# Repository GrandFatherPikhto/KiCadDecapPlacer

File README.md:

# KiCadSpoke v1.20.0

**KiCadSpoke** is a command-line layout automation and PCB cloning tool for automated placement in **KiCad**, block replication, and routing of components and vias in KiCad based on **templates** and **roles**:

- Moving components (capacitors, resistors, ferrites, crystals, etc.) to specified positions.
- Creating vias attached to the spoke as a whole or to individual components.
- **Cloning** repetitive functional blocks (PI-filters, DAC channels) at different locations on the board.
- Automatic component selection by **roles** and **nets** without specifying explicit refdes.
- Idempotency: repeated runs do not duplicate already correctly placed items.
- Undo of the last operation.
- Extracting templates from the current selection on the board with net parametrisation and custom origin selection.
- Snapshotting channels (for hierarchical projects) via a file‑based cloner (`clone-extract`).
- **Template transformation** (rotation, mirroring, origin shift) using the separate script `transform_template.py`.

---

## Key Features

An advanced script-based alternative to the traditional KiCad Replicate Layout plugin, designed for complex multi-channel projects and automated design reuse via IPC API.

- **Template-based approach** – geometry is described once in local coordinates and can be rotated/translated for each application.
- **Automatic component selection** – instead of refdes, roles are used (`LIGHT`, `HEAVY`, `PI_FILTER_C1`, etc.). Specific instances are taken from a pool by net and the `Role` field in the schematic.
- **Section cloning** (`ClonePlacement`) – supports two modes:
  - **by selection** – for one‑off instances (e.g., a single MCU);
  - **by nets** – for repeatedly repeated blocks (with net name parametrisation via placeholders and `params`). In this mode, ambiguity is resolved by physical proximity to the anchor (if components are electrically indistinguishable but located close to different anchors).
- **Generalised vias** – vias can be at the spoke level and at the component level; all coordinates are relative to the spoke origin, making them independent of actual pad positions.
- **Placement registry** – stores UUIDs of created vias, ensuring idempotency and automatic cleanup of obsolete entries. Now reconciliation is performed against real vias on the board, not only the JSON record, to avoid desynchronisation.
- **Pre‑validation** – config checks before any board modifications (template/pad existence, component pool sufficiency, clone correctness, and resolved via nets existence on the board).
- **Diagnostics** – a set of scripts for debugging IPC, geometry, and field reading.
- **File‑based cloner** (`clone-extract`) – parses `.net` and `.kicad_pcb` without IPC, builds a twin map of channels for hierarchical projects.
- **Template transformation** – the script `utils/transform_template.py` allows rotating, mirroring, and shifting the origin of existing templates without re‑extracting from the board.
- **Enhanced `extract`** – when extracting a template, you can set the origin to a specific via or component (instead of the bbox) and parameterise nets (replace literals with patterns containing placeholders).

---

## Installation and Dependencies

### Requirements
- Python 3.8 or later.
- KiCad 8.0 or later (with IPC API enabled).
- The **kipy** library (Python wrapper for KiCad IPC).

### Installation
```bash
pip install kipy pyyaml sexpdata
```
(For diagnostics, `psutil` may be required.)

### Setting up Roles in the Schematic (Eeschema)
Before using the tool, you need to add a custom field `Role` to components that should participate in placement:
1. Open the symbol in Eeschema.
2. Add a field named **Role** with a value matching the role in the template (e.g., `LIGHT`, `HEAVY`).
3. Run **Update PCB from Schematic** to propagate the field to the board.
4. Verify field readability with the diagnostic script:
   ```bash
   python -m kicadspoke.diagnostics.test_custom_field C5 --field Role
   ```

---

## Key Concepts

### Template (SpokeTemplate)
A template describes the **local geometry** of one "spoke" – a set of components and vias relative to a local origin (0,0) in the `along/across` coordinate system. It contains:
- **`vias`** – vias at the spoke level (usually the power net).
- **`components`** – a list of slots, each with a `role`, local coordinates, angle, and a list of vias (usually to GND).

All coordinates are defined **once** at `rotation_deg=0`; when applied, the template is rotated as a whole.

#### Template layer (`layer`)
Each template now has an absolute layer (`F.Cu` or `B.Cu`), which is automatically set during extraction (`extract`). Components lying on a different layer receive an explicit `layer` in their slot.

#### Net parametrisation during extraction
When extracting a template, you can replace literal net names with patterns containing placeholders using the `--net-template` and `--param` options of the `extract` command. This eliminates manual YAML editing.

### Spoke (ManualSpoke)
Attaches a template to a specific IC pin:
- `pad` – pad number of the target component.
- `shift_x_mm`, `shift_y_mm` – flat shift from the pad centre to the template origin.
- `rotation_deg` – rotation of the entire template.

**Important:** In new config versions, each rule (`rules`) must have its own `anchor_ref` (anchor component). The global `target_ref` has been removed.

### Roles and Component Pool
Instead of refdes, **roles** are used in the config. For each net (`rule.net`), a pool of components is built, where each component:
- Has a `Role` field with the required value.
- Has at least one pad connected to that net.

Components are sorted in natural numeric order (`C5` < `C10`) and consumed in the order of spokes.

### Cloning (ClonePlacement)
Allows applying a template at an arbitrary point on the board, without tying to IC pads. Supports:
- **Selection mode** – reads roles from the current selection in the PCB editor.
- **Net mode** – for each role, a net is specified (via `nets` or `net_template` with placeholders resolved by `params` and `net_overrides`). If multiple candidates are electrically indistinguishable, the tool can pick the one closest to the anchor (if the distance margin is sufficient). This is useful for power filters on a common rail.

### Placement Registry (PlacementRegistry)
Stores each via's UUID, position, parameters, and net in a JSON file next to the config. On subsequent runs:
- already correctly placed vias are skipped;
- those that changed position/parameters are deleted and recreated;
- obsolete entries (keys not present in the new plan) are removed (prune).

**Important:** Reconciliation now checks against real vias on the board (`adapter.get_vias()`), not only the JSON record, preventing desynchronisation due to manual deletions or crashes between registry write and board commit.

### Net Resolution (`net_resolution`)
For cloned templates, net names go through a three‑step resolution:
1. **Literal** – if no placeholders.
2. **Placeholder** – substitution from `params` (e.g., `{channel}` → `2`).
3. **net_overrides** – final override of the resolved name (for hierarchical paths).

During extraction, the reverse operation (`--net-template`) is available, turning literals into patterns.

### Template Transformation (`transform_template.py`)
A separate script for post‑processing templates:
- **Rotation** by an arbitrary angle.
- **Mirroring** along the X or Y axis.
- **Origin shift** to a specified via (by index or net name) or component (by index or role), or explicit offset.

This allows quick adaptation of a template to different orientations without re‑extracting.

---

## Configuration File Format (YAML)

### Root Parameters (new)

| Field | Type | Description |
|-------|------|-------------|
| `layer` | string | Global layer for ManualSpoke rules: `"F.Cu"` or `"B.Cu"` (replaces deprecated `side`). |
| `templates` | dict | Named spoke templates. |
| `rules` | list | Manual spoke rules, each with `anchor_ref`. |
| `clone_placements` | list | Cloned placements (TemplatePlacer). |
| `thermal_via_array` | dict | Thermal via settings (optional). |
| `place_components` | boolean | Enable component moves (default `true`). |
| `skip_existing_components` | boolean | Skip components and vias already in place. |
| `via_keepout_clearance_mm`, `via_search_step_mm`, `via_search_max_radius_mm`, `via_search_n_directions` | numbers | Parameters for thermal via placement search. |

**Deprecated fields:** `target_ref` and `side` at the root are no longer supported (fatal error on load).

### Template (`templates`) – now with `layer`

```yaml
templates:
  cap_pair_standard:
    layer: B.Cu       # absolute layer of the template
    vias:
      - offset_along_mm: 0.0
        offset_across_mm: -1.5
        drill_mm: 0.3
        diameter_mm: 0.6
        # net omitted – for ManualSpoke uses rule.net, for ClonePlacement must be explicit
    components:
      - role: LIGHT
        offset_along_mm: 1.0
        offset_across_mm: -1.0
        angle_deg: 90.0
        vias:
          - offset_along_mm: 0.0
            offset_across_mm: -1.0
            net: GND
            drill_mm: 0.3
            diameter_mm: 0.6
      - role: HEAVY
        offset_along_mm: 1.0
        offset_across_mm: 2.0
        angle_deg: 270.0
        vias:
          - offset_along_mm: 0.0
            offset_across_mm: 1.3
            net: GND
            drill_mm: 0.3
            diameter_mm: 0.6
```

### Manual Spokes (`rules`) – now with `anchor_ref`

```yaml
rules:
- net: +1V2_VCCINT
  anchor_ref: IC1       # mandatory field – anchor for this rule
  spokes:
  - pad: '109'
    template: cap_pair_standard
    shift_x_mm: 0.0
    shift_y_mm: 0.0
    rotation_deg: 90.0
  - pad: '62'
    template: cap_pair_standard
    shift_x_mm: 0.4
    shift_y_mm: 0.0
    rotation_deg: 270.0
```

### Cloned Placements (`clone_placements`) – new fields

```yaml
clone_placements:
  - name: dac_channel_2
    template: dac_channel
    anchor_ref: IC1
    anchor_pad: '17'      # optional
    origin_x_mm: -10.0
    origin_y_mm: -10.0
    rotation_deg: 90.0
    params:
      channel: 2
    nets:
      CAP_IN: "GPIO12"
      CAP_OUT: "GPIO12_FILTERED"
    net_overrides:
      "/STM32F4xx/BOOT0": "/STM32F4xx_2/BOOT0"
    layer: B.Cu          # explicit placement layer (if different from template layer)
    mirror: true         # mirror the whole construction (requires layer change)
    refs:                # explicit role -> ref mapping (last resort)
      DAC_PI_FILTER_C1: C601
    enabled: true
```

- If `anchor_ref` is set, `origin_x/y` become a **shift** from the anchor.
- `layer` and `mirror` allow placing the template on the opposite side with mirroring.

### Thermal Vias (`thermal_via_array`) – `target_ref` renamed to `anchor_ref`

```yaml
thermal_via_array:
  enabled: true
  anchor_ref: IC1       # was target_ref
  pad: '145'
  net: GND
  rows: 4
  cols: 4
  margin_mm: 0.5
  pattern: grid
  drill_mm: 0.3
  diameter_mm: 0.5
```

---

## CLI Commands

All commands are run via `kicadspoke_cli.py`. If the subcommand is omitted, `apply` is assumed.

### `apply` – apply placement

```bash
python kicadspoke_cli.py apply config.yaml [options]
```

Options:
- `--dry-run` – only show the plan, do not apply changes.
- `--timeout-ms` – IPC timeout in ms (default 20000).
- `--batch-size` – batch size for commits (default 10).
- `--verbose` – verbose output (DEBUG).
- `--log-file` – save logs to a file.
- `--no-collision-check` – disable collision checking.
- `--collision-margin` – margin for collision checking in mm (default 0.2).
- `--clone-placement NAME` – process only the specified clone (useful for debugging).

### `extract` – extract template from selection (enhanced)

```bash
python kicadspoke_cli.py extract --name template_name --output config.yaml [--verbose] [--log-file] [--param KEY=VALUE] [--net-template LITERAL=PATTERN] [--origin-by-via-net NET] [--origin-by-component-role ROLE]
```

New options:
- `--param KEY=VALUE` – sets a parameter for verifying `--net-template` (e.g., `channel=1`). Not written to the template, only used for validation.
- `--net-template LITERAL=PATTERN` – replaces a real net with a pattern containing a placeholder (e.g., `DAC1_DB1=DAC{channel}_DB1`). Can be repeated.
- `--origin-by-via-net NET` – sets the template origin to the position of the via with the specified net (instead of the bbox lower-left corner). Fatal if no such via or more than one exists.
- `--origin-by-component-role ROLE` – sets the origin to the position of the component with the specified role.

Before running, select the desired components and vias in the PCB editor. Roles must be unique.

### `undo` – undo the last operation

```bash
python kicadspoke_cli.py undo [--verbose] [--log-file]
```

### `clone-extract` – snapshot a channel (file‑based cloner)

```bash
python kicadspoke_cli.py clone-extract --net project.net --pcb project.kicad_pcb --channel Channel_0 --output snapshot.yaml [--verbose]
```

Analyzes a hierarchical project, extracts all components, tracks, and vias belonging to the specified channel, and saves the snapshot in YAML. Useful for studying the channel structure before writing a clone config.

### `transform_template.py` – separate tool for template transformation

This script is located in `utils/` and is used for post‑processing existing YAML templates:

```bash
python utils/transform_template.py -i input.yaml -o output.yaml --rotate 90 --mirror-x --set-origin-by-via-net "GND"
```

Options:
- `--rotate DEG` – rotate counter‑clockwise by angle (degrees).
- `--mirror-x` – mirror along the X axis (flips `across` sign).
- `--mirror-y` – mirror along the Y axis (flips `along` sign).
- `--set-origin-by-via-index N` – shift origin to the via with index N.
- `--set-origin-by-via-net NET` – shift origin to the via with the given net.
- `--set-origin-by-component-index N` – shift origin to the component with index N.
- `--set-origin-by-component-role ROLE` – shift origin to the component with the given role.
- `--origin-x X --origin-y Y` – explicit origin offset.

Order of application: first origin shift (if set), then rotation and mirroring.

---

## Usage Examples

### 1. Standard run
```bash
python kicadspoke_cli.py 10CL006YE144C8G.yaml
```

### 2. Dry run (preview only)
```bash
python kicadspoke_cli.py config.yaml --dry-run
```

### 3. Process a single clone when multiple clones are in selection mode
```bash
python kicadspoke_cli.py config.yaml --clone-placement pi_filter_vccio
```

### 4. Extract a template with parametrisation and origin by via
Select elements on the board, then:
```bash
python kicadspoke_cli.py extract --name my_filter --output my_config.yaml --net-template "DAC1_DB1=DAC{channel}_DB1" --param channel=1 --origin-by-via-net "/Channel_0/DAC/+3V3_CLKVDD" --verbose
```

### 5. Transform a template
```bash
python utils/transform_template.py -i my_template.yaml -o my_template_rotated.yaml --rotate 180 --set-origin-by-component-role FB
```

### 6. Undo
```bash
python kicadspoke_cli.py undo --verbose
```

---

## Diagnostics and Known Issues

### KiCad Bug #24966 (crash on first write via IPC)
When the Schematic Editor is open and no interactive edit has been made in the session, calling `Board.update_items()` (even with no changes) can crash KiCad (null pointer in `API_HANDLER_EDITOR::checkForBusy`). The request is dispatched to the schematic handler, which is not initialised.

**Symptoms:** KiCad silently closes, the client receives `ConnectionError: Error receiving reply from KiCad: Timed out`.

**Workaround:** before running `apply`, either close the schematic editor or perform any interactive edit in PCB (move a component and save). The code includes a warning (`check_write_crash_risk`) and retries with backoff, but the crash remains possible – it's a KiCad defect.

### Diagnostic scripts
The folder `kicadspoke/diagnostics/` contains scripts for debugging:
- `diagnose_first_write_crash.py` – runs a ladder of reads/writes to localise the crash.
- `test_custom_fields.py` – checks reading of the `Role` field.
- `test_move_one_cap.py` – minimal test for moving a component.
- `test_flip_one_cap.py` – tests flip via GUI action.
- `test_create_one_via.py` – tests via creation.
- `test_pad_mirror_convention.py` – empirical check of pad mirroring on flip.
- `get_selected_component.py` – prints information about selected components.

---

## Project Structure (brief)

```
kicadspoke/
├── kicadspoke_cli.py          # CLI entry point
├── config.py                  # YAML loading → dataclasses
├── constants.py               # Global constants
├── exceptions.py              # Exception hierarchy
├── validation.py              # Pre‑validation checks (including via net existence)
├── registry.py                # Via registry (reconcile with live vias)
├── net_resolution.py          # Net resolution for ClonePlacement and reverse parametrisation
├── template_extraction.py     # Template extraction (with new options)
├── undo.py                    # Undo operation
├── geometry/                  # Geometry calculations (spoke_layout, keepout, thermal_grid, pad_projection, clone_geometry)
├── kicad/                     # KiCad IPC adapter
├── placement/                 # Planner, executors, services (collision, planner, executor, services)
│   ├── services/              # Including clone_role_resolver with anchor‑proximity disambiguation
├── cloner/                    # File‑based cloner (extract, netlist, pcb, models, sexp)
├── diagnostics/               # Diagnostic scripts
├── utils/                     # Utilities (units, transform_template.py)
└── tests/                     # Unit and integration tests
```

---

## 📚 Technical Documentation

Detailed descriptions of architecture, modules, and API are in the `docs/` folder:

- [Project architecture](./docs/architect.md)
- [CLI commands](./docs/commands.md)
- [Diagnostics](./docs/diagnostics.md)
- [Geometry utilities](./docs/geometry.md)
- [KiCad adapter](./docs/kicad.md)
- [Using kipy](./docs/kipy.md)
- [Placement planning and execution](./docs/placement.md)
- [Tests](./docs/tests.md)
- [Top‑level modules](./docs/uplevel_modules.md)
- [File‑based cloner](./docs/cloner.md)
- [Template transformation](./docs/rotate_template.md) (new)

---

## License

This project is distributed under the **MIT** license. See the `LICENSE` file for details.

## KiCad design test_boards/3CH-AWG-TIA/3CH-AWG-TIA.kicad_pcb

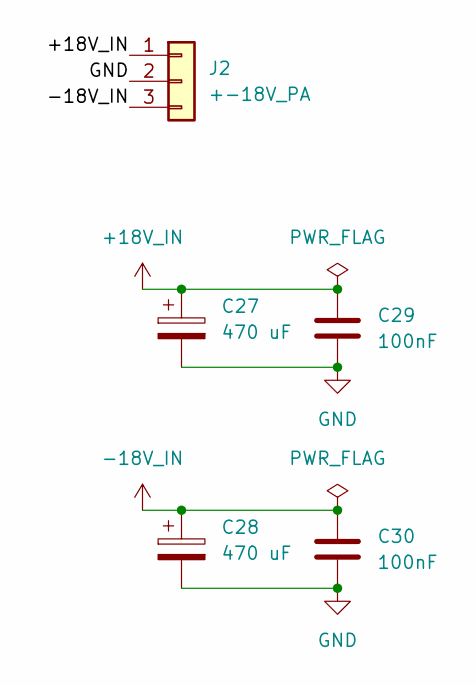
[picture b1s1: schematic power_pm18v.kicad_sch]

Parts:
C27, C28: 470 uF; CP_Radial_D10.0mm_P5.00mm
C29, C30: 100nF; C_0603_1608Metric_Pad1.08x0.95mm_HandSolder
J2: +-18V_PA; KF3013P

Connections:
+18V_IN: C27.1, C29.1, J2.1; also elsewhere on the board
-18V_IN: C28.1, C30.1, J2.3; also elsewhere on the board
GND: C27.2, C28.2, C29.2, C30.2, J2.2; also elsewhere on the board

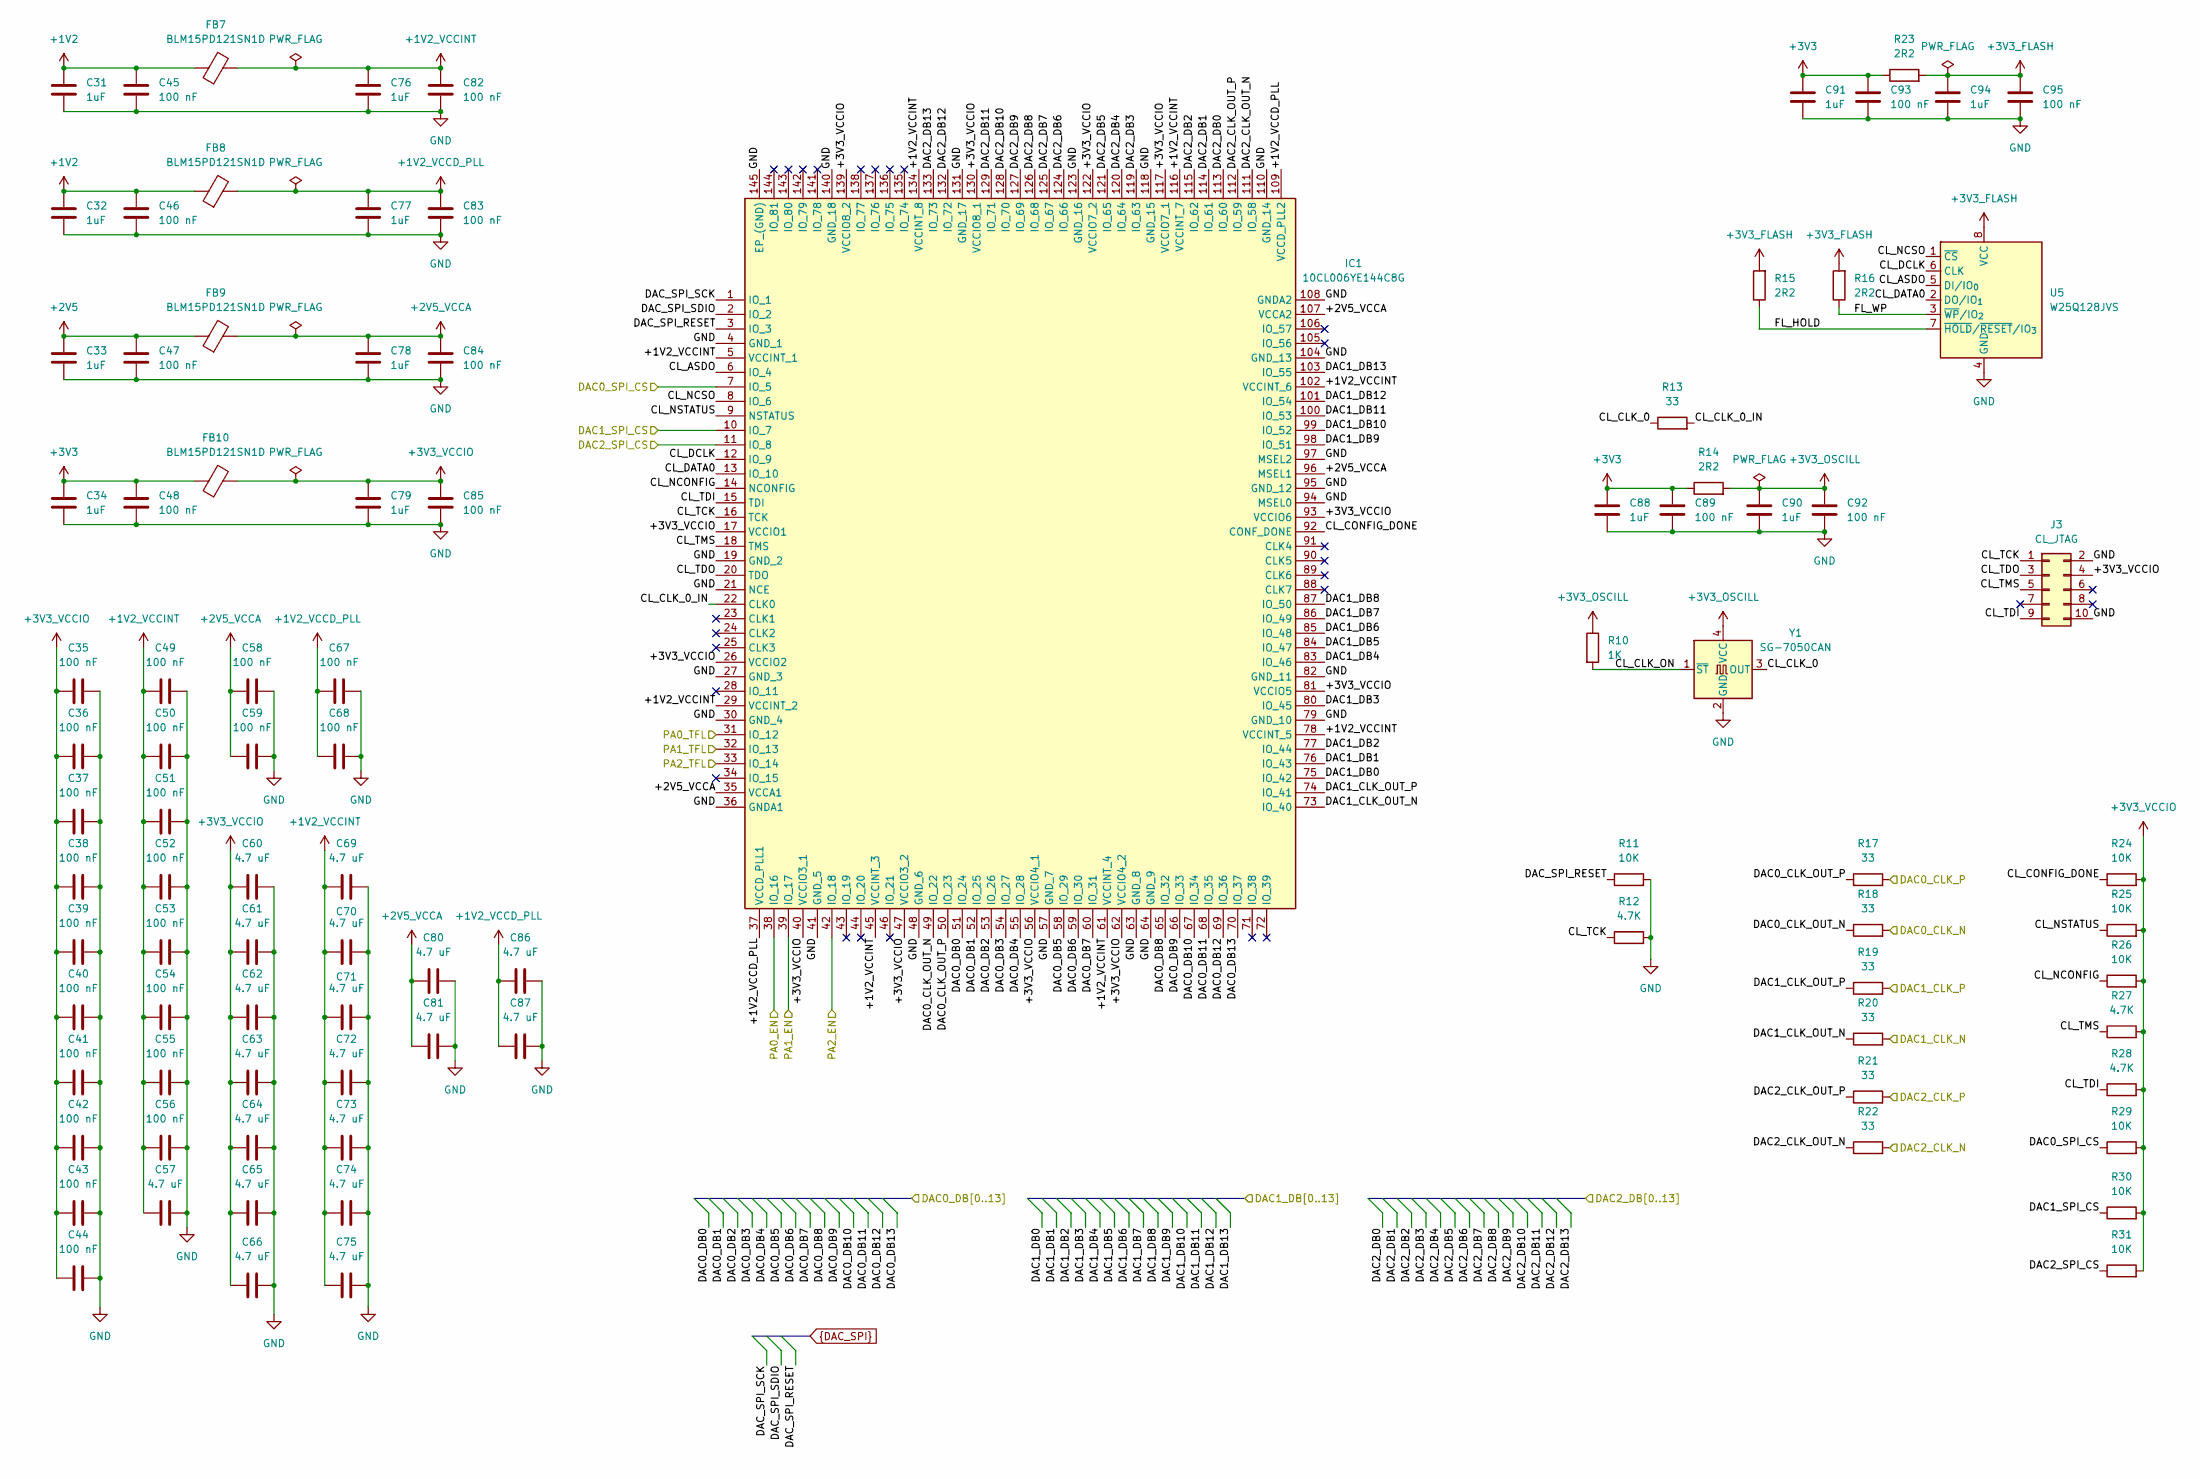
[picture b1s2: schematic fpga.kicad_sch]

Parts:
C31, C32, C33, C34, C76, C77, C78, C79, C88, C90, C91, C94: 1uF; C_0603_1608Metric_Pad1.08x0.95mm_HandSolder
C35, C36, C37, C38, C39, C40, C41, C42, C43, C44, C45, C46, C47, C48, C49, C50, C51, C52, C53, C54, C55, C56, C58, C59, C67, C68, C82, C83, C84, C85, C89, C92, C93, C95: 100 nF; C_0402_1005Metric_Pad0.74x0.62mm_HandSolder
C57, C60, C61, C62, C63, C64, C65, C66, C69, C70, C71, C72, C73, C74, C75, C80, C81, C86, C87: 4.7 uF; C_0603_1608Metric_Pad1.08x0.95mm_HandSolder
FB7, FB8, FB9, FB10: BLM15PD121SN1D; L_0402_1005Metric
IC1: 10CL006YE144C8G; QFP50P2200X2200X165-145N; Manufacturer_Part_Number 10CL006YE144C8G; Mouser Part Number 989-10CL006YE144C8G
J3: CL_JTAG; IDC-Header_2x05_P2.54mm_Vertical
R10: 1K; R_0402_1005Metric_Pad0.72x0.64mm_HandSolder
R11, R24, R25, R26, R29, R30, R31: 10K; R_0402_1005Metric_Pad0.72x0.64mm_HandSolder
R12, R27, R28: 4.7K; R_0402_1005Metric_Pad0.72x0.64mm_HandSolder
R13, R17, R18, R19, R20, R21, R22: 33; R_0402_1005Metric_Pad0.72x0.64mm_HandSolder
R14, R15, R16, R23: 2R2; R_0402_1005Metric_Pad0.72x0.64mm_HandSolder
U5: W25Q128JVS; SOIC-8_5.3x5.3mm_P1.27mm
Y1: SG-7050CAN; Oscillator_SMD_SeikoEpson_SG8002CA-4Pin_7.0x5.0mm

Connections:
+1V2: C31.1, C32.1, C45.1, C46.1, FB7.1, FB8.1; also elsewhere on the board
+1V2_VCCD_PLL: C67.1, C68.1, C77.1, C83.1, C86.1, C87.1, FB8.2, IC1.37 (VCCD_PLL1), IC1.109 (VCCD_PLL2)
+1V2_VCCINT: C49.1, C50.1, C51.1, C52.1, C53.1, C54.1, C55.1, C56.1, C57.1, C69.1, C70.1, C71.1, C72.1, C73.1, C74.1, C75.1, C76.1, C82.1, FB7.2, IC1.5 (VCCINT_1), IC1.29 (VCCINT_2), IC1.45 (VCCINT_3), IC1.61 (VCCINT_4), IC1.78 (VCCINT_5), IC1.102 (VCCINT_6), IC1.116 (VCCINT_7), IC1.134 (VCCINT_8)
+2V5: C33.1, C47.1, FB9.1; also elsewhere on the board
+2V5_VCCA: C58.1, C59.1, C78.1, C80.1, C81.1, C84.1, FB9.2, IC1.35 (VCCA1), IC1.96 (MSEL1), IC1.107 (VCCA2)
+3V3: C34.1, C48.1, C88.1, C89.1, C91.1, C93.1, FB10.1, R14.1, R23.1; also elsewhere on the board
+3V3_FLASH: C94.1, C95.2, R15.2, R16.2, R23.2, U5.8 (VCC)
+3V3_OSCILL: C90.1, C92.2, R10.1, R14.2, Y1.4 (VCC)
+3V3_VCCIO: C35.1, C36.1, C37.1, C38.1, C39.1, C40.1, C41.1, C42.1, C43.1, C44.1, C60.1, C61.1, C62.1, C63.1, C64.1, C65.1, C66.1, C79.1, C85.1, FB10.2, IC1.17 (VCCIO1), IC1.26 (VCCIO2), IC1.40 (VCCIO3_1), IC1.47 (VCCIO3_2), IC1.56 (VCCIO4_1), IC1.62 (VCCIO4_2), IC1.81 (VCCIO5), IC1.93 (VCCIO6), IC1.117 (VCCIO7_1), IC1.122 (VCCIO7_2), IC1.130 (VCCIO8_1), IC1.139 (VCCIO8_2), J3.4, R24.2, R25.2, R26.2, R27.2, R28.2, R29.2, R30.2, R31.2
/Channel_0/DAC_CLK_N: R18.2; also elsewhere on the board
/Channel_0/DAC_CLK_P: R17.2; also elsewhere on the board
/Channel_0/DAC_DB0: IC1.51 (IO_24); also elsewhere on the board
/Channel_0/DAC_DB1: IC1.52 (IO_25); also elsewhere on the board
/Channel_0/DAC_DB2: IC1.53 (IO_26); also elsewhere on the board
/Channel_0/DAC_DB3: IC1.54 (IO_27); also elsewhere on the board
/Channel_0/DAC_DB4: IC1.55 (IO_28); also elsewhere on the board
/Channel_0/DAC_DB5: IC1.58 (IO_29); also elsewhere on the board
/Channel_0/DAC_DB6: IC1.59 (IO_30); also elsewhere on the board
/Channel_0/DAC_DB7: IC1.60 (IO_31); also elsewhere on the board
/Channel_0/DAC_DB8: IC1.65 (IO_32); also elsewhere on the board
/Channel_0/DAC_DB9: IC1.66 (IO_33); also elsewhere on the board
/Channel_0/DAC_DB10: IC1.67 (IO_34); also elsewhere on the board
/Channel_0/DAC_DB11: IC1.68 (IO_35); also elsewhere on the board
/Channel_0/DAC_DB12: IC1.69 (IO_36); also elsewhere on the board
/Channel_0/DAC_DB13: IC1.70 (IO_37); also elsewhere on the board
/Channel_0/PA_EN: IC1.38 (IO_16); also elsewhere on the board
/Channel_0/TFL/CL_TFL_SIGNAL: IC1.31 (IO_12); also elsewhere on the board
/Channel_1/DAC_CLK_N: R20.2; also elsewhere on the board
/Channel_1/DAC_CLK_P: R19.2; also elsewhere on the board
/Channel_1/DAC_DB0: IC1.75 (IO_42); also elsewhere on the board
/Channel_1/DAC_DB1: IC1.76 (IO_43); also elsewhere on the board
/Channel_1/DAC_DB2: IC1.77 (IO_44); also elsewhere on the board
/Channel_1/DAC_DB3: IC1.80 (IO_45); also elsewhere on the board
/Channel_1/DAC_DB4: IC1.83 (IO_46); also elsewhere on the board
/Channel_1/DAC_DB5: IC1.84 (IO_47); also elsewhere on the board
/Channel_1/DAC_DB6: IC1.85 (IO_48); also elsewhere on the board
/Channel_1/DAC_DB7: IC1.86 (IO_49); also elsewhere on the board
/Channel_1/DAC_DB8: IC1.87 (IO_50); also elsewhere on the board
/Channel_1/DAC_DB9: IC1.98 (IO_51); also elsewhere on the board
/Channel_1/DAC_DB10: IC1.99 (IO_52); also elsewhere on the board
/Channel_1/DAC_DB11: IC1.100 (IO_53); also elsewhere on the board
/Channel_1/DAC_DB12: IC1.101 (IO_54); also elsewhere on the board
/Channel_1/DAC_DB13: IC1.103 (IO_55); also elsewhere on the board
/Channel_1/PA_EN: IC1.39 (IO_17); also elsewhere on the board
/Channel_1/TFL/CL_TFL_SIGNAL: IC1.32 (IO_13); also elsewhere on the board
/Channel_2/DAC_CLK_N: R22.2; also elsewhere on the board
/Channel_2/DAC_CLK_P: R21.2; also elsewhere on the board
/Channel_2/DAC_DB0: IC1.113 (IO_60); also elsewhere on the board
/Channel_2/DAC_DB1: IC1.114 (IO_61); also elsewhere on the board
/Channel_2/DAC_DB2: IC1.115 (IO_62); also elsewhere on the board
/Channel_2/DAC_DB3: IC1.119 (IO_63); also elsewhere on the board
/Channel_2/DAC_DB4: IC1.120 (IO_64); also elsewhere on the board
/Channel_2/DAC_DB5: IC1.121 (IO_65); also elsewhere on the board
/Channel_2/DAC_DB6: IC1.124 (IO_66); also elsewhere on the board
/Channel_2/DAC_DB7: IC1.125 (IO_67); also elsewhere on the board
/Channel_2/DAC_DB8: IC1.126 (IO_68); also elsewhere on the board
/Channel_2/DAC_DB9: IC1.127 (IO_69); also elsewhere on the board
/Channel_2/DAC_DB10: IC1.128 (IO_70); also elsewhere on the board
/Channel_2/DAC_DB11: IC1.129 (IO_71); also elsewhere on the board
/Channel_2/DAC_DB12: IC1.132 (IO_72); also elsewhere on the board
/Channel_2/DAC_DB13: IC1.133 (IO_73); also elsewhere on the board
/Channel_2/PA_EN: IC1.42 (IO_18); also elsewhere on the board
/Channel_2/TFL/CL_TFL_SIGNAL: IC1.33 (IO_14); also elsewhere on the board
/FPGA/CL_ASDO: IC1.6 (IO_4), U5.5 (DI/IO_{0})
/FPGA/CL_CLK_0: R13.1, Y1.3 (OUT)
/FPGA/CL_CLK_0_IN: IC1.22 (CLK0), R13.2
/FPGA/CL_CLK_ON: R10.2, Y1.1 (~ST)
/FPGA/CL_CONFIG_DONE: IC1.92 (CONF_DONE), R24.1
/FPGA/CL_DATA0: IC1.13 (IO_10), U5.2 (DO/IO_{1})
/FPGA/CL_DCLK: IC1.12 (IO_9), U5.6 (CLK)
/FPGA/CL_NCONFIG: IC1.14 (NCONFIG), R26.1
/FPGA/CL_NCSO: IC1.8 (IO_6), U5.1 (~CS)
/FPGA/CL_NSTATUS: IC1.9 (NSTATUS), R25.1
/FPGA/CL_TCK: IC1.16 (TCK), J3.1, R12.1
/FPGA/CL_TDI: IC1.15 (TDI), J3.9, R28.1
/FPGA/CL_TDO: IC1.20 (TDO), J3.3
/FPGA/CL_TMS: IC1.18 (TMS), J3.5, R27.1
/FPGA/DAC0_CLK_OUT_N: IC1.49 (IO_22), R18.1
/FPGA/DAC0_CLK_OUT_P: IC1.50 (IO_23), R17.1
/FPGA/DAC0_SPI_CS: IC1.7 (IO_5), R29.1; also elsewhere on the board
/FPGA/DAC1_CLK_OUT_N: IC1.73 (IO_40), R20.1
/FPGA/DAC1_CLK_OUT_P: IC1.74 (IO_41), R19.1
/FPGA/DAC1_SPI_CS: IC1.10 (IO_7), R30.1; also elsewhere on the board
/FPGA/DAC2_CLK_OUT_N: IC1.111 (IO_58), R22.1
/FPGA/DAC2_CLK_OUT_P: IC1.112 (IO_59), R21.1
/FPGA/DAC2_SPI_CS: IC1.11 (IO_8), R31.1; also elsewhere on the board
/FPGA/FL_HOLD: R15.1, U5.7 (~HOLD/~RESET/IO_{3})
/FPGA/FL_WP: R16.1, U5.3 (~WP/IO_{2})
DAC_SPI_RESET: IC1.3 (IO_3), R11.1; also elsewhere on the board
DAC_SPI_SCK: IC1.1 (IO_1); also elsewhere on the board
DAC_SPI_SDIO: IC1.2 (IO_2); also elsewhere on the board
GND: C31.2, C32.2, C33.2, C34.2, C35.2, C36.2, C37.2, C38.2, C39.2, C40.2, C41.2, C42.2, C43.2, C44.2, C45.2, C46.2, C47.2, C48.2, C49.2, C50.2, C51.2, C52.2, C53.2, C54.2, C55.2, C56.2, C57.2, C58.2, C59.2, C60.2, C61.2, C62.2, C63.2, C64.2, C65.2, C66.2, C67.2, C68.2, C69.2, C70.2, C71.2, C72.2, C73.2, C74.2, C75.2, C76.2, C77.2, C78.2, C79.2, C80.2, C81.2, C82.2, C83.2, C84.2, C85.2, C86.2, C87.2, C88.2, C89.2, C90.2, C91.2, C92.1, C93.2, C94.2, C95.1, IC1.4 (GND_1), IC1.19 (GND_2), IC1.21 (NCE), IC1.27 (GND_3), IC1.30 (GND_4), IC1.36 (GNDA1), IC1.41 (GND_5), IC1.48 (GND_6), IC1.57 (GND_7), IC1.63 (GND_8), IC1.64 (GND_9), IC1.79 (GND_10), IC1.82 (GND_11), IC1.94 (MSEL0), IC1.95 (GND_12), IC1.97 (MSEL2), IC1.104 (GND_13), IC1.108 (GNDA2), IC1.110 (GND_14), IC1.118 (GND_15), IC1.123 (GND_16), IC1.131 (GND_17), IC1.140 (GND_18), IC1.145 (EP_(GND)), J3.2, J3.10, R11.2, R12.2, U5.4 (GND), Y1.2 (GND); also elsewhere on the board

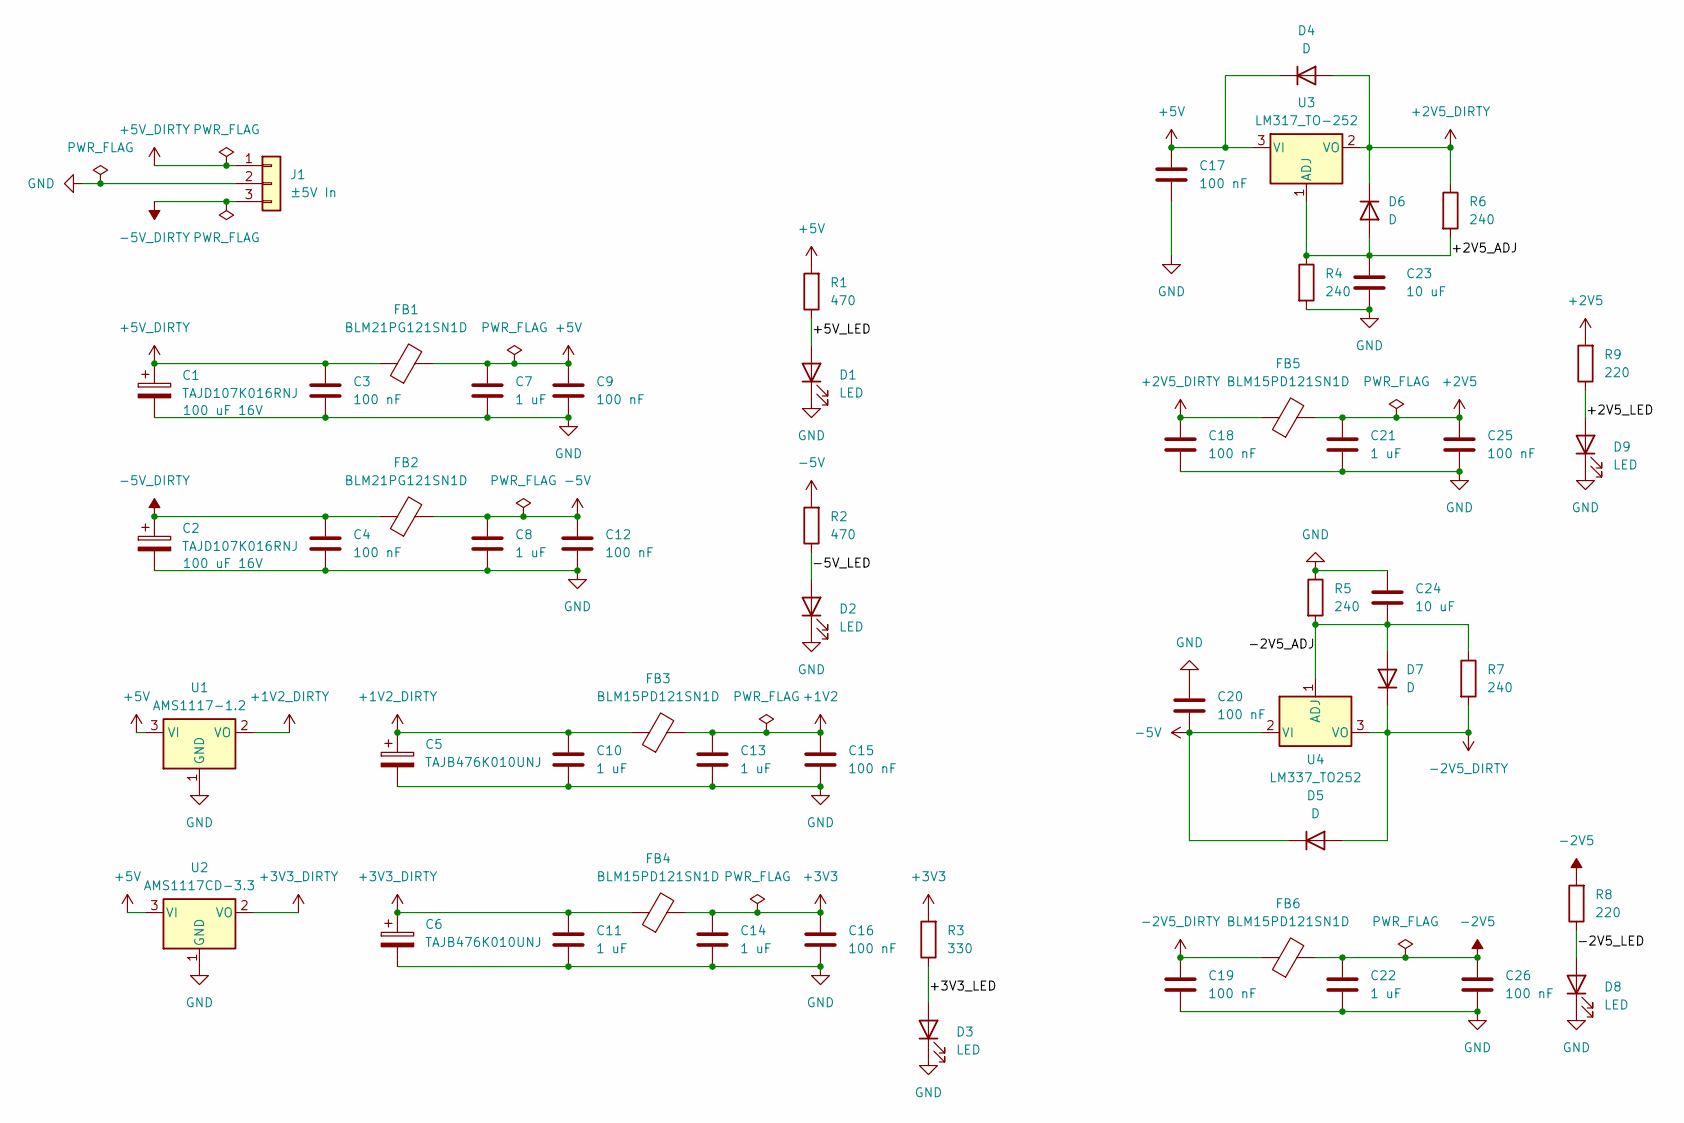
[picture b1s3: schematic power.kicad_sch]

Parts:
C1, C2: TAJD107K016RNJ; CP_EIA-7343-20_Kemet-V_HandSolder
C3, C4, C9, C12, C15, C16, C17, C18, C19, C20, C25, C26: 100 nF; C_0603_1608Metric_Pad1.08x0.95mm_HandSolder
C5, C6: TAJB476K010UNJ; CP_EIA-3528-12_Kemet-T_HandSolder
C7, C8, C10, C11, C13, C14, C21, C22: 1 uF; C_1206_3216Metric_Pad1.33x1.80mm_HandSolder
C23, C24: 10 uF; C_1206_3216Metric_Pad1.33x1.80mm_HandSolder
D1, D2, D3, D8, D9: LED; D_0805_2012Metric_Pad1.15x1.40mm_HandSolder
D4, D5, D6, D7: D; D_SMA_Handsoldering
FB1, FB2: BLM21PG121SN1D; L_0805_2012Metric
FB3, FB4, FB5, FB6: BLM15PD121SN1D; L_0402_1005Metric
J1: ±5V In; JST_XH_B3B-XH-A_1x03_P2.50mm_Vertical
R1, R2: 470; R_0603_1608Metric_Pad0.98x0.95mm_HandSolder
R3: 330; R_0603_1608Metric_Pad0.98x0.95mm_HandSolder
R4, R5, R6, R7: 240; R_0603_1608Metric_Pad0.98x0.95mm_HandSolder
R8, R9: 220; R_0603_1608Metric_Pad0.98x0.95mm_HandSolder
U1: AMS1117-1.2; SOT-223-3_TabPin2
U2: AMS1117CD-3.3; TO-252-3_TabPin2
U3: LM317_TO-252; TO-252-2
U4: LM337_TO252; TO-252-2

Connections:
+1V2: C13.1, C15.1, FB3.2; also elsewhere on the board
+1V2_DIRTY: C5.1, C10.1, FB3.1, U1.2 (VO)
+2V5: C21.1, C25.1, FB5.2, R9.2; also elsewhere on the board
+2V5_DIRTY: C18.1, D4.2 (A), D6.1 (K), FB5.1, R6.1, U3.2 (VO)
+3V3: C14.1, C16.1, FB4.2, R3.2; also elsewhere on the board
+3V3_DIRTY: C6.1, C11.1, FB4.1, U2.2 (VO)
+5V: C7.1, C9.1, C17.2, D4.1 (K), FB1.2, R1.2, U1.3 (VI), U2.3 (VI), U3.3 (VI)
+5V_DIRTY: C1.1, C3.1, FB1.1, J1.1
-2V5: C22.1, C26.1, FB6.2, R8.2; also elsewhere on the board
-2V5_DIRTY: C19.1, D5.2 (A), D7.1 (K), FB6.1, R7.2, U4.3 (VO)
-5V: C8.1, C12.1, C20.1, D5.1 (K), FB2.2, R2.2, U4.2 (VI)
-5V_DIRTY: C2.1, C4.1, FB2.1, J1.3
/Power/+2V5_ADJ: C23.1, D6.2 (A), R4.1, R6.2, U3.1 (ADJ)
/Power/+2V5_LED: D9.2 (A), R9.1
/Power/+3V3_LED: D3.2 (A), R3.1
/Power/+5V_LED: D1.2 (A), R1.1
/Power/-2V5_ADJ: C24.2, D7.2 (A), R5.2, R7.1, U4.1 (ADJ)
/Power/-2V5_LED: D8.2 (A), R8.1
/Power/-5V_LED: D2.2 (A), R2.1
GND: C1.2, C2.2, C3.2, C4.2, C5.2, C6.2, C7.2, C8.2, C9.2, C10.2, C11.2, C12.2, C13.2, C14.2, C15.2, C16.2, C17.1, C18.2, C19.2, C20.2, C21.2, C22.2, C23.2, C24.1, C25.2, C26.2, D1.1 (K), D2.1 (K), D3.1 (K), D8.1 (K), D9.1 (K), J1.2, R4.2, R5.1, U1.1 (GND), U2.1 (GND); also elsewhere on the board

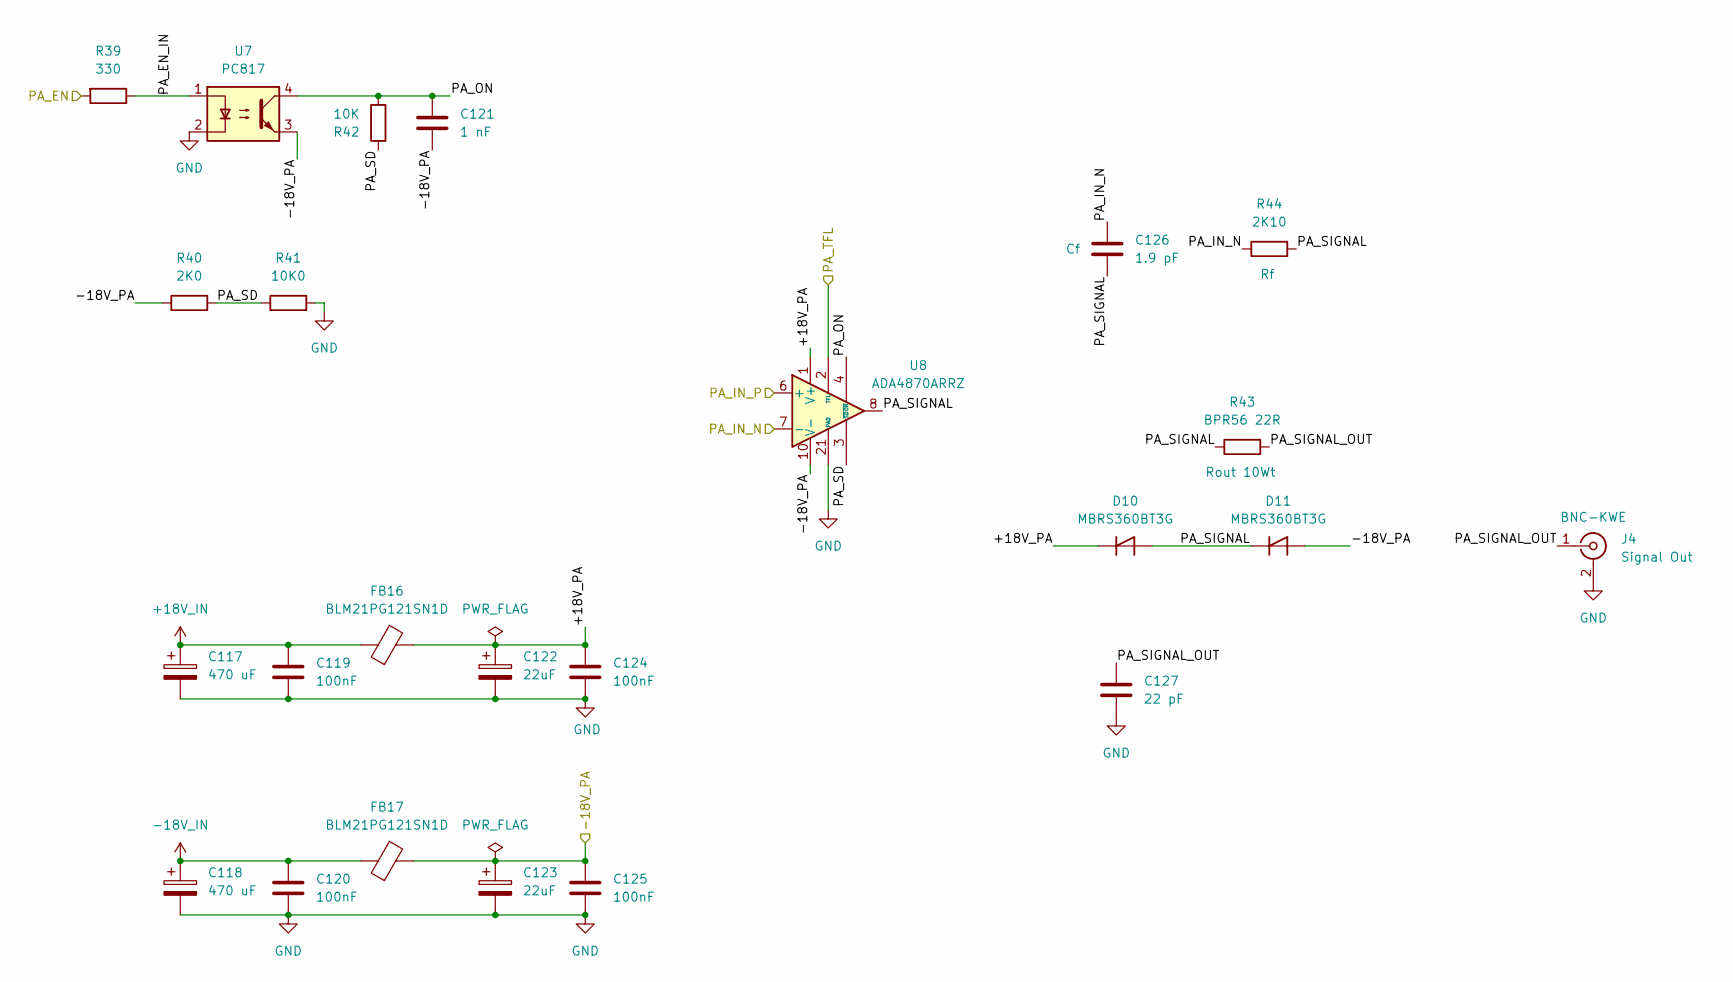
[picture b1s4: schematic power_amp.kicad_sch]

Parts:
C117, C118: 470 uF; CP_Radial_D10.0mm_P5.00mm
C119, C120, C124, C125: 100nF; C_0603_1608Metric_Pad1.08x0.95mm_HandSolder
C121: 1 nF; C_0603_1608Metric_Pad1.08x0.95mm_HandSolder
C122, C123: 22uF; CP_EIA-7343-20_Kemet-V
C126: 1.9 pF; C_0603_1608Metric_Pad1.08x0.95mm_HandSolder
C127: 22 pF; C_0603_1608Metric_Pad1.08x0.95mm_HandSolder
D10, D11: MBRS360BT3G; D_SMC
FB16, FB17: BLM21PG121SN1D; L_0805_2012Metric
J4: Signal Out; BNC_TEConnectivity_1478035_Horizontal
R39: 330; R_0603_1608Metric_Pad0.98x0.95mm_HandSolder
R40: 2K0; R_0603_1608Metric_Pad0.98x0.95mm_HandSolder
R41: 10K0; R_0603_1608Metric_Pad0.98x0.95mm_HandSolder
R42: 10K; R_0603_1608Metric_Pad0.98x0.95mm_HandSolder
R43: BPR56 22R; R_Axial_Power_L50.0mm_W9.0mm_P55.88mm
R44: 2K10; R_0603_1608Metric_Pad0.98x0.95mm_HandSolder
U7: PC817; DIP-4_W7.62mm
U8: ADA4870ARRZ; HSOP-20-1EP_11.0x15.9mm_P1.27mm_SlugDown_ThermalVias

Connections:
+18V_IN: C117.1, C119.1, FB16.1; also elsewhere on the board
-18V_IN: C118.1, C120.1, FB17.1; also elsewhere on the board
/Channel_0/OpAmp/PA_IN_P: U8.6 (+); also elsewhere on the board
/Channel_0/PA_EN: R39.2; also elsewhere on the board
/Channel_0/Power Amplifier Sheet/+18V_PA: C122.1, C124.1, D10.1 (K), FB16.2, U8.1 (V+), U8.18 (V+), U8.19 (V+), U8.20 (V+)
/Channel_0/Power Amplifier Sheet/-18V_PA: C121.2, C123.1, C125.1, D11.2 (A), FB17.2, R40.1, U7.3, U8.10 (V-), U8.11 (V-), U8.12 (V-), U8.13 (V-); also elsewhere on the board
/Channel_0/Power Amplifier Sheet/PA_EN_IN: R39.1, U7.1
/Channel_0/Power Amplifier Sheet/PA_IN_N: C126.1, R44.1, U8.7 (-); also elsewhere on the board
/Channel_0/Power Amplifier Sheet/PA_ON: C121.1, R42.2, U7.4, U8.4 (~ON)
/Channel_0/Power Amplifier Sheet/PA_SD: R40.2, R41.1, R42.1, U8.3 (~SD)
/Channel_0/Power Amplifier Sheet/PA_SIGNAL: C126.2, D10.2 (A), D11.1 (K), R43.1, R44.2, U8.8, U8.14, U8.15, U8.16, U8.17
/Channel_0/Power Amplifier Sheet/PA_SIGNAL_OUT: C127.1, J4.1 (In), R43.2
/Channel_0/Power Amplifier Sheet/PA_TFL: U8.2 (TFL); also elsewhere on the board
GND: C117.2, C118.2, C119.2, C120.2, C122.2, C123.2, C124.2, C125.2, C127.2, J4.2 (Ext), R41.2, U7.2, U8.21 (PAD); also elsewhere on the board

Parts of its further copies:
C151, C152, C185, C186: 470 uF; CP_Radial_D10.0mm_P5.00mm
C153, C154, C158, C159, C187, C188, C192, C193: 100nF; C_0603_1608Metric_Pad1.08x0.95mm_HandSolder
C155, C189: 1 nF; C_0603_1608Metric_Pad1.08x0.95mm_HandSolder
C156, C157, C190, C191: 22uF; CP_EIA-7343-20_Kemet-V
C160, C194: 1.9 pF; C_0603_1608Metric_Pad1.08x0.95mm_HandSolder
C161, C195: 22 pF; C_0603_1608Metric_Pad1.08x0.95mm_HandSolder
D13, D14, D16, D17: MBRS360BT3G; D_SMC
FB23, FB24, FB30, FB31: BLM21PG121SN1D; L_0805_2012Metric
J5, J6: Signal Out; BNC_TEConnectivity_1478035_Horizontal
R55, R71: 330; R_0603_1608Metric_Pad0.98x0.95mm_HandSolder
R56, R72: 2K0; R_0603_1608Metric_Pad0.98x0.95mm_HandSolder
R57, R73: 10K0; R_0603_1608Metric_Pad0.98x0.95mm_HandSolder
R58, R74: 10K; R_0603_1608Metric_Pad0.98x0.95mm_HandSolder
R59, R75: BPR56 22R; R_Axial_Power_L50.0mm_W9.0mm_P55.88mm
R60, R76: 2K10; R_0603_1608Metric_Pad0.98x0.95mm_HandSolder
U11, U15: PC817; DIP-4_W7.62mm
U12, U16: ADA4870ARRZ; HSOP-20-1EP_11.0x15.9mm_P1.27mm_SlugDown_ThermalVias

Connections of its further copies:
+18V_IN: C151.1, C153.1, C185.1, C187.1, FB23.1, FB30.1; also elsewhere on the board
-18V_IN: C152.1, C154.1, C186.1, C188.1, FB24.1, FB31.1; also elsewhere on the board
/Channel_1/OpAmp/PA_IN_P: U12.6 (+); also elsewhere on the board
/Channel_1/PA_EN: R55.2; also elsewhere on the board
/Channel_1/Power Amplifier Sheet/+18V_PA: C156.1, C158.1, D13.1 (K), FB23.2, U12.1 (V+), U12.18 (V+), U12.19 (V+), U12.20 (V+)
/Channel_1/Power Amplifier Sheet/-18V_PA: C155.2, C157.1, C159.1, D14.2 (A), FB24.2, R56.1, U11.3, U12.10 (V-), U12.11 (V-), U12.12 (V-), U12.13 (V-); also elsewhere on the board
/Channel_1/Power Amplifier Sheet/PA_EN_IN: R55.1, U11.1
/Channel_1/Power Amplifier Sheet/PA_IN_N: C160.1, R60.1, U12.7 (-); also elsewhere on the board
/Channel_1/Power Amplifier Sheet/PA_ON: C155.1, R58.2, U11.4, U12.4 (~ON)
/Channel_1/Power Amplifier Sheet/PA_SD: R56.2, R57.1, R58.1, U12.3 (~SD)
/Channel_1/Power Amplifier Sheet/PA_SIGNAL: C160.2, D13.2 (A), D14.1 (K), R59.1, R60.2, U12.8, U12.14, U12.15, U12.16, U12.17
/Channel_1/Power Amplifier Sheet/PA_SIGNAL_OUT: C161.1, J5.1 (In), R59.2
/Channel_1/Power Amplifier Sheet/PA_TFL: U12.2 (TFL); also elsewhere on the board
/Channel_2/OpAmp/PA_IN_P: U16.6 (+); also elsewhere on the board
/Channel_2/PA_EN: R71.2; also elsewhere on the board
/Channel_2/Power Amplifier Sheet/+18V_PA: C190.1, C192.1, D16.1 (K), FB30.2, U16.1 (V+), U16.18 (V+), U16.19 (V+), U16.20 (V+)
/Channel_2/Power Amplifier Sheet/-18V_PA: C189.2, C191.1, C193.1, D17.2 (A), FB31.2, R72.1, U15.3, U16.10 (V-), U16.11 (V-), U16.12 (V-), U16.13 (V-); also elsewhere on the board
/Channel_2/Power Amplifier Sheet/PA_EN_IN: R71.1, U15.1
/Channel_2/Power Amplifier Sheet/PA_IN_N: C194.1, R76.1, U16.7 (-); also elsewhere on the board
/Channel_2/Power Amplifier Sheet/PA_ON: C189.1, R74.2, U15.4, U16.4 (~ON)
/Channel_2/Power Amplifier Sheet/PA_SD: R72.2, R73.1, R74.1, U16.3 (~SD)
/Channel_2/Power Amplifier Sheet/PA_SIGNAL: C194.2, D16.2 (A), D17.1 (K), R75.1, R76.2, U16.8, U16.14, U16.15, U16.16, U16.17
/Channel_2/Power Amplifier Sheet/PA_SIGNAL_OUT: C195.1, J6.1 (In), R75.2
/Channel_2/Power Amplifier Sheet/PA_TFL: U16.2 (TFL); also elsewhere on the board
GND: C151.2, C152.2, C153.2, C154.2, C156.2, C157.2, C158.2, C159.2, C161.2, C185.2, C186.2, C187.2, C188.2, C190.2, C191.2, C192.2, C193.2, C195.2, J5.2 (Ext), J6.2 (Ext), R57.2, R73.2, U11.2, U12.21 (PAD), U15.2, U16.21 (PAD); also elsewhere on the board
